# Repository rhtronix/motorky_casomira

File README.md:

motorky_casomira
================

Motorky - časomíra. BT displej, čtečky...

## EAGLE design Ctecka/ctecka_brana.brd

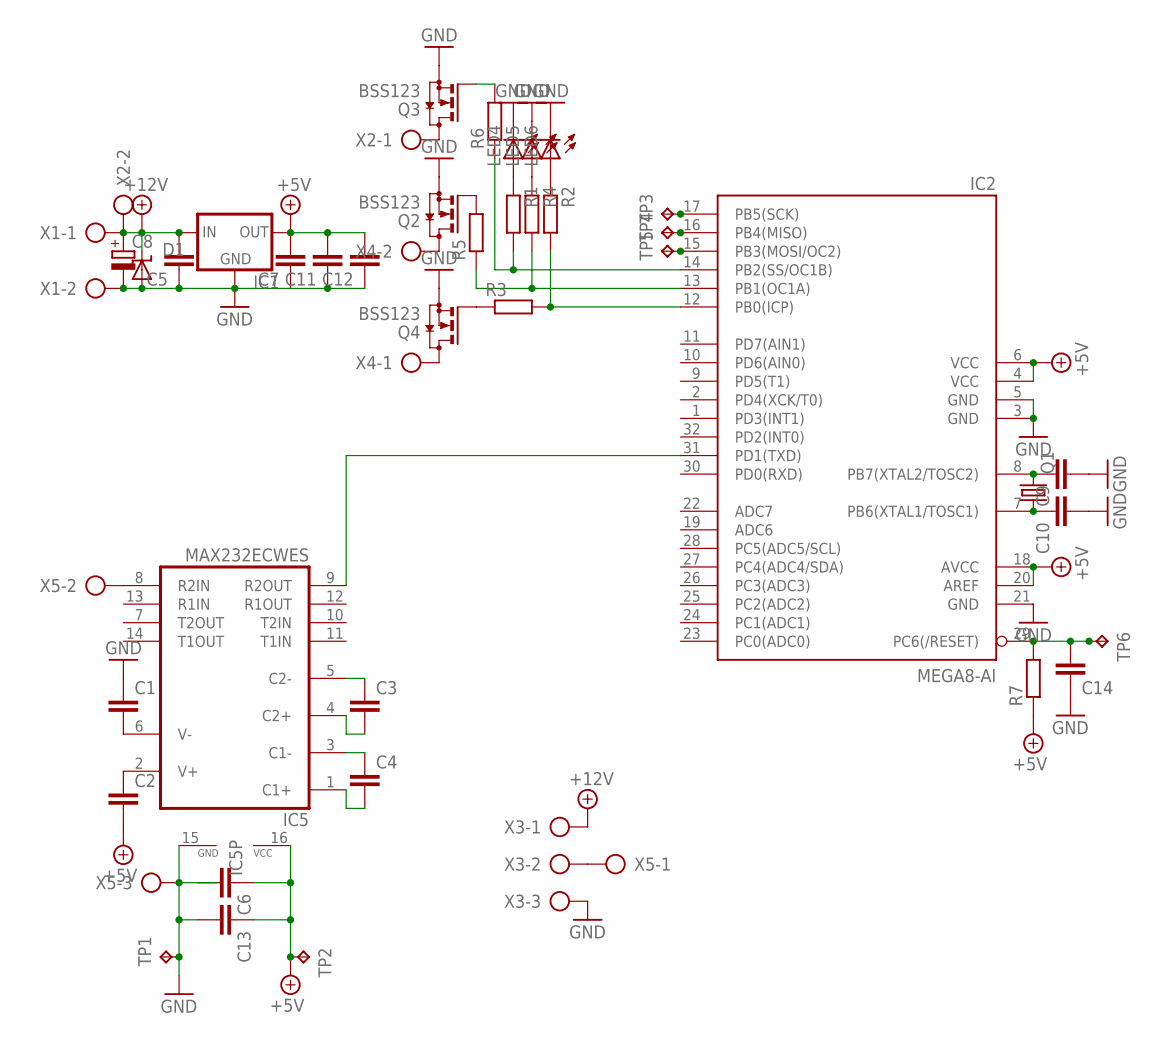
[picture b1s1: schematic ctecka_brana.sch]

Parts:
C1, C2, C3, C4, C5, C6, C7, C9, C10, C11, C12, C13, C14: C-EUC0603; C0603
C8: CPOL-EUSMCD; SMC_D
D1: SUPPRESSOR-SMBG; SMBG
IC1: 78LXXF; SOT89R
IC2: MEGA8-AI; TQFP32-08
IC5: MAX232ECWES; SO16
LED4, LED5, LED6: LEDCHIP-LED0805; CHIP-LED0805
Q1: CRYSTALCTS406; CTS406
Q2, Q3, Q4: BSS123; SOT23
R1, R2, R3, R4, R5, R6, R7: R-EU_R0603; R0603
TP1, TP2, TP3, TP4, TP5, TP6: TPB1,27; B1,27
X1, X2, X4: AK500/2
X3, X5: AK500/3

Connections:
+5V: C2.2, C6.1, C7.2, C11.2, C12.2, C13.1, IC1.2 (OUT), IC2.4 (VCC), IC2.6 (VCC), IC2.18 (AVCC), IC2.20 (AREF), IC5.16 (VCC), R7.1, TP2.TP
+12V: C5.2, C8.+, D1.C, IC1.1 (IN), X1.1, X2.2, X3.1
GND: C1.1, C5.1, C6.2, C7.1, C8.-, C9.2, C10.2, C11.1, C12.1, C13.2, C14.1, D1.A, IC1.3 (GND), IC2.3 (GND), IC2.5 (GND), IC2.21 (GND), IC5.15 (GND), LED4.C, LED5.C, LED6.C, Q2.2 (S), Q3.2 (S), Q4.2 (S), TP1.TP, X1.2, X3.3, X5.3
unnamed: IC2.17 (PB5(SCK)), TP3.TP
unnamed: IC2.15 (PB3(MOSI/OC2)), TP5.TP
unnamed: Q3.3 (D), X2.1
unnamed: IC2.31 (PD1(TXD)), IC5.9 (R2OUT)
unnamed: C3.1, IC5.5 (C2-)
unnamed: C4.1, IC5.3 (C1-)
unnamed: C1.2, IC5.6 (V-)
unnamed: C2.1, IC5.2 (V+)
unnamed: X3.2, X5.1
unnamed: IC5.8 (R2IN), X5.2
unnamed: C4.2, IC5.1 (C1+)
unnamed: C3.2, IC5.4 (C2+)
unnamed: IC2.16 (PB4(MISO)), TP4.TP
unnamed: C14.2, IC2.29 (PC6(/RESET)), R7.2, TP6.TP
unnamed: C9.1, IC2.8 (PB7(XTAL2/TOSC2)), Q1.3 (2)
unnamed: C10.1, IC2.7 (PB6(XTAL1/TOSC1)), Q1.1
unnamed: Q2.1 (G), R5.2
unnamed: Q2.3 (D), X4.2
unnamed: Q4.1 (G), R3.1
unnamed: Q4.3 (D), X4.1
unnamed: LED4.A, R1.1
unnamed: LED5.A, R4.1
unnamed: LED6.A, R2.1
unnamed: Q3.1 (G), R6.2
unnamed: IC2.12 (PB0(ICP)), R2.2, R3.2
unnamed: IC2.13 (PB1(OC1A)), R4.2, R5.1
unnamed: IC2.14 (PB2(SS/OC1B)), R1.2, R6.1

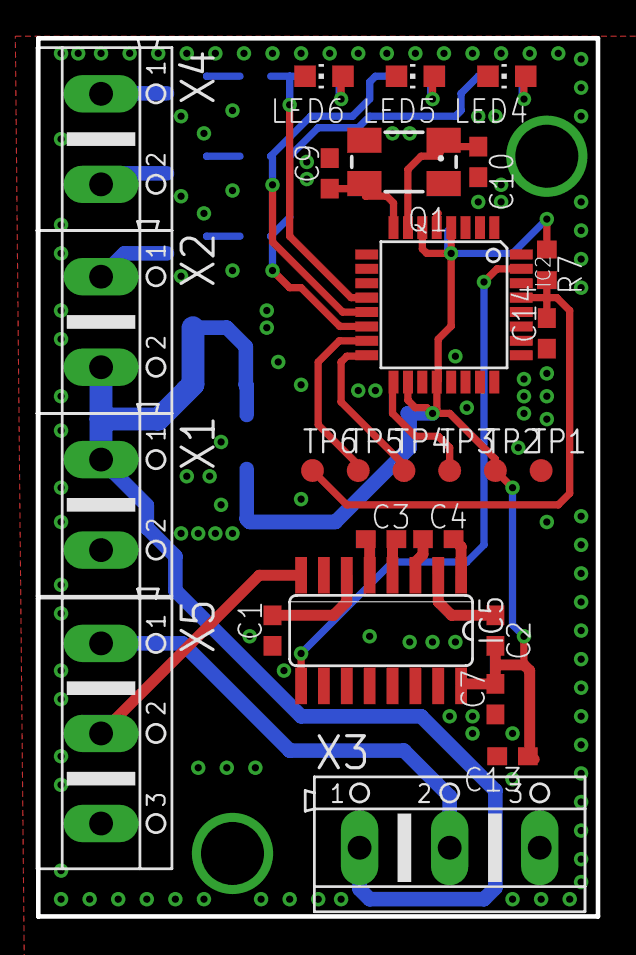
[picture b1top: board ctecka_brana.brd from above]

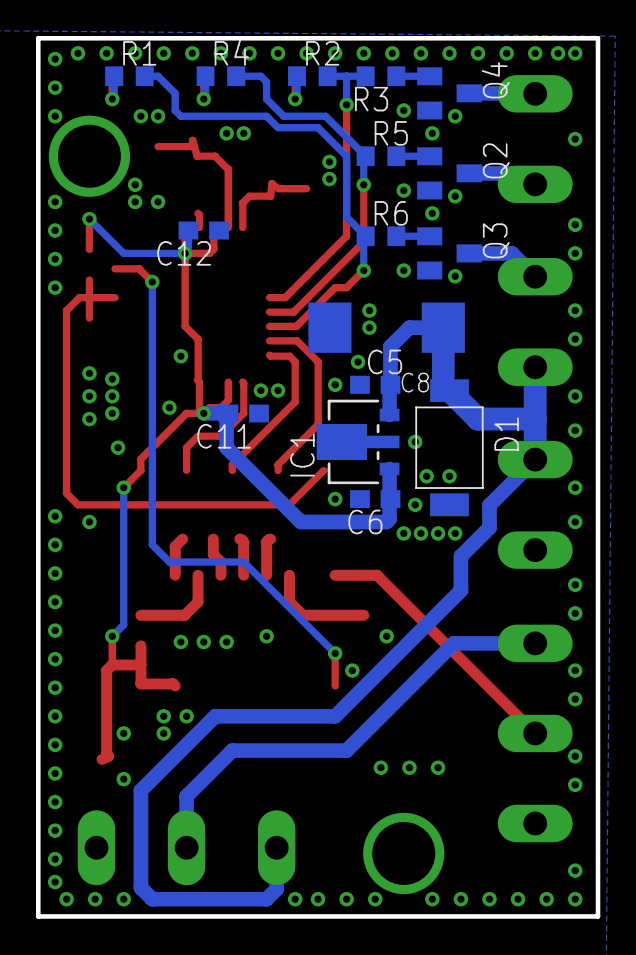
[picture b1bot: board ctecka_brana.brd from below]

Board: 2 copper layers, 31.1 x 48.8 mm, 43 parts (16 on the bottom side), 30 nets.

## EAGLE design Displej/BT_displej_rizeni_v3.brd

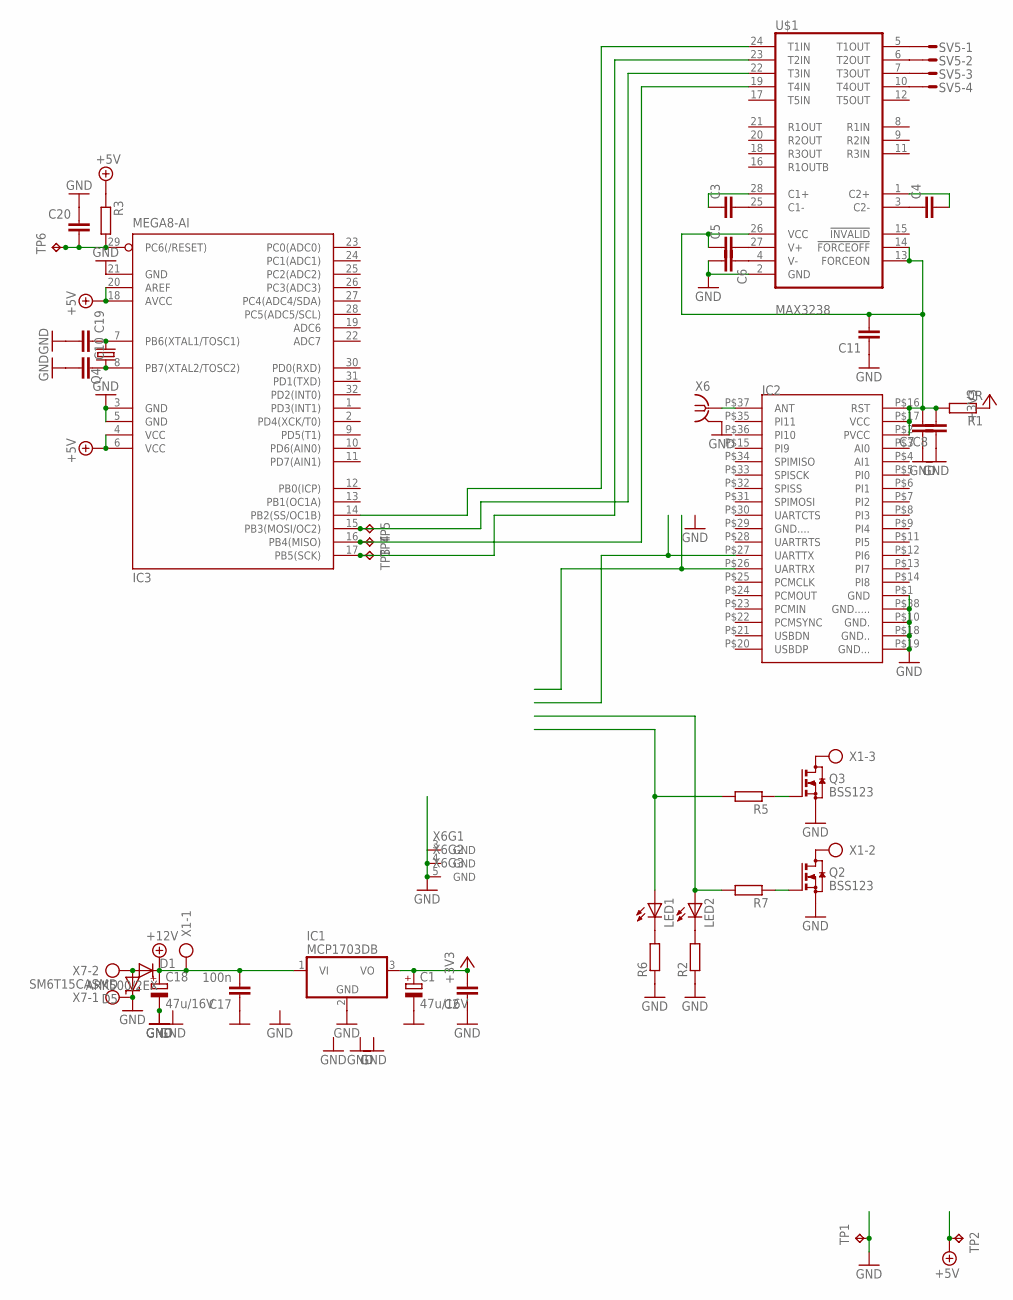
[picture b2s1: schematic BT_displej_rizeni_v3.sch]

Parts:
C1, C18: 47u/16V; SMC_C
C2, C3, C4, C5, C6, C7, C8, C10, C11, C19, C20: C-EUC0603; C0603
C17: 100n; C0603
D1: DIODE-DO214AC; DO214AC
D5: SM6T15CASMD; SMBJ
IC1: MCP1703DB; SOT223
IC2: BT220; B_DIL
IC3: MEGA8-AI; TQFP32-08
LED1, LED2: LEDCHIP-LED0805; CHIP-LED0805
Q2, Q3: BSS123; SOT23
Q4: CRYSTALCTS406; CTS406
R1: 0R; R0603
R2, R3, R5, R6, R7: R-EU_R0603; R0603
SV5: S04P
TP1, TP2, TP3, TP4, TP5, TP6: TPB1,27; B1,27
U$1: MAX3238; SSOP28
X1: AK500/3
X6: BU-SMA-V
X7: ARK500/2EX; AK500/2

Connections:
+3V3: C1.+, C2.2, IC1.3 (VO), R1.1
+5V: IC3.4 (VCC), IC3.6 (VCC), IC3.18 (AVCC), IC3.20 (AREF), R3.1, TP2.TP
+12V: C17.2, C18.+, D1.C, IC1.1 (VI), X1.1
GND: C1.-, C2.1, C6.2, C7.1, C8.1, C10.2, C11.1, C17.1, C18.-, C19.2, C20.1, D5.C, IC1.2 (GND), IC2.P$1 (GND), IC2.P$10 (GND.), IC2.P$18 (GND..), IC2.P$19 (GND...), IC2.P$38 (GND.....), IC3.3 (GND), IC3.5 (GND), IC3.21 (GND), Q2.2 (S), Q3.2 (S), R2.1, R6.1, TP1.TP, U$1.2 (GND), X6.2 (GND), X6.3 (GND), X6.4 (GND), X6.5 (GND), X7.1
unnamed: SV5.1, U$1.5 (T1OUT)
unnamed: LED2.C, R2.2
unnamed: Q3.1 (G), R5.1
unnamed: D1.A, D5.A, X7.2
unnamed: LED1.C, R6.2
unnamed: LED1.A, R5.2
unnamed: LED2.A, R7.2
unnamed: Q3.3 (D), X1.3
unnamed: Q2.3 (D), X1.2
unnamed: Q2.1 (G), R7.1
unnamed: SV5.2, U$1.6 (T2OUT)
unnamed: SV5.3, U$1.7 (T3OUT)
unnamed: SV5.4, U$1.10 (T4OUT)
unnamed: C3.2, U$1.25 (C1-)
unnamed: IC3.14 (PB2(SS/OC1B)), U$1.24 (T1IN)
unnamed: C4.1, U$1.3 (C2-)
unnamed: C3.1, U$1.28 (C1+)
unnamed: IC3.17 (PB5(SCK)), TP3.TP, U$1.23 (T2IN)
unnamed: IC3.15 (PB3(MOSI/OC2)), TP5.TP, U$1.22 (T3IN)
unnamed: IC3.16 (PB4(MISO)), TP4.TP, U$1.19 (T4IN)
unnamed: C4.2, U$1.1 (C2+)
unnamed: C5.2, U$1.27 (V+)
unnamed: C6.1, U$1.4 (V-)
unnamed: C5.1, C7.2, C8.2, C11.2, IC2.P$2 (PVCC), IC2.P$16 (RST), IC2.P$17 (VCC), R1.2, U$1.13 (FORCEON), U$1.14 (!FORCEOFF), U$1.26 (VCC)
unnamed: IC2.P$37 (ANT), X6.1
unnamed: C10.1, IC3.8 (PB7(XTAL2/TOSC2)), Q4.3 (2)
unnamed: C19.1, IC3.7 (PB6(XTAL1/TOSC1)), Q4.1
unnamed: C20.2, IC3.29 (PC6(/RESET)), R3.2, TP6.TP

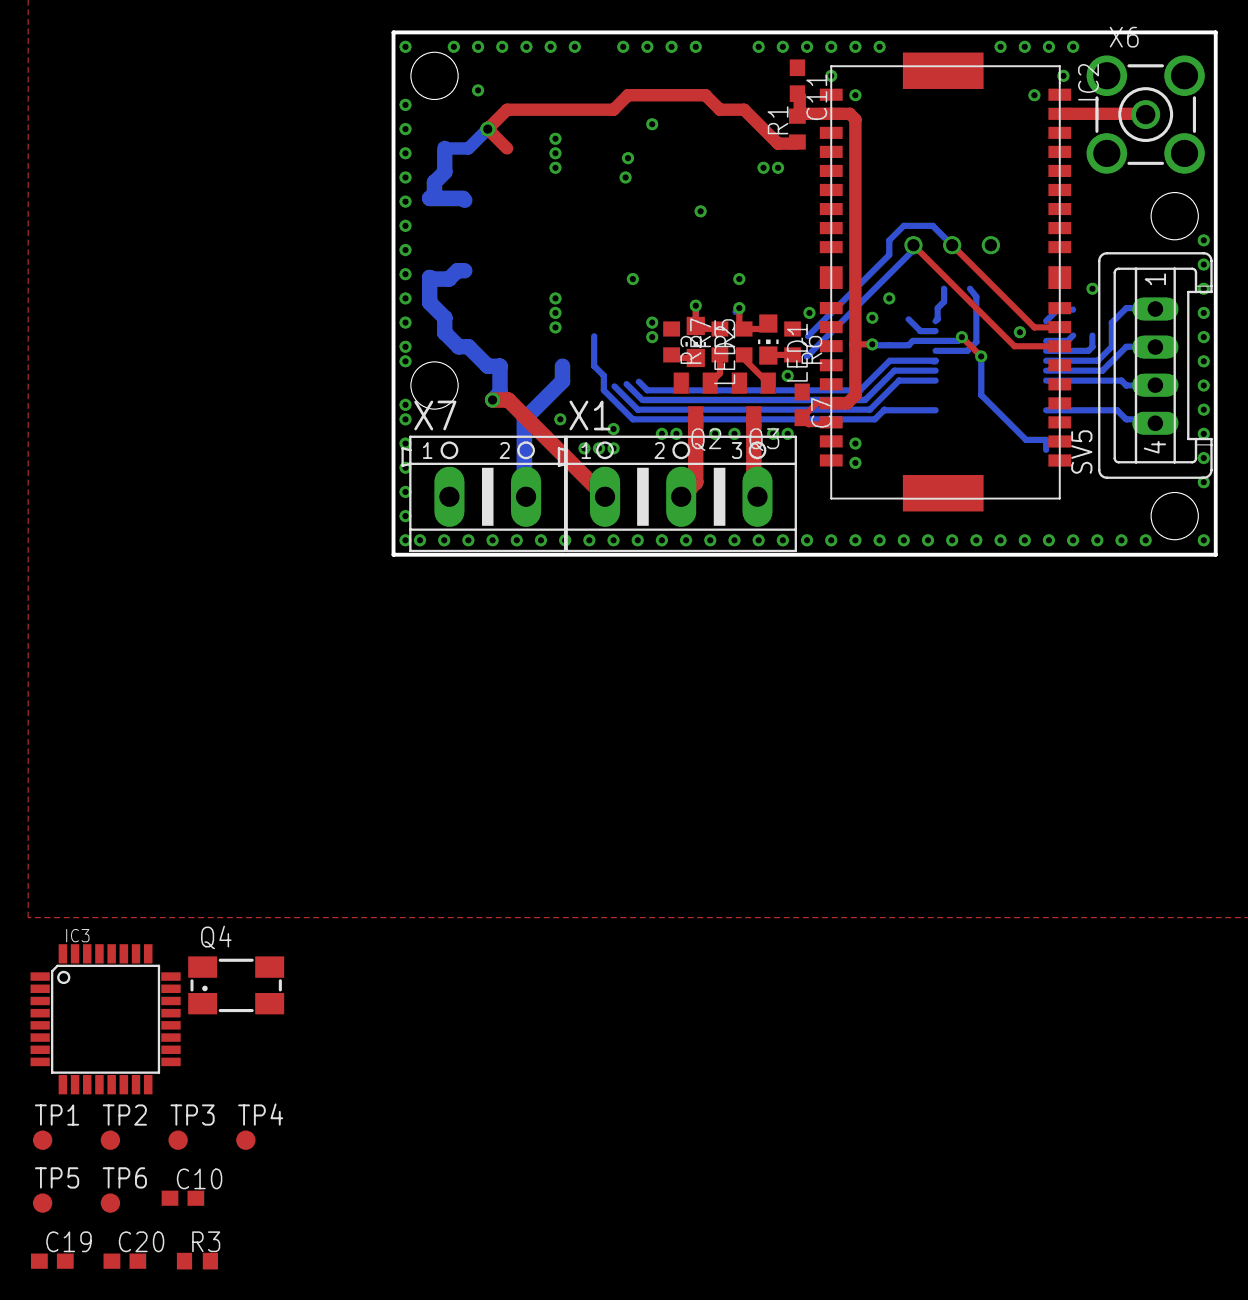
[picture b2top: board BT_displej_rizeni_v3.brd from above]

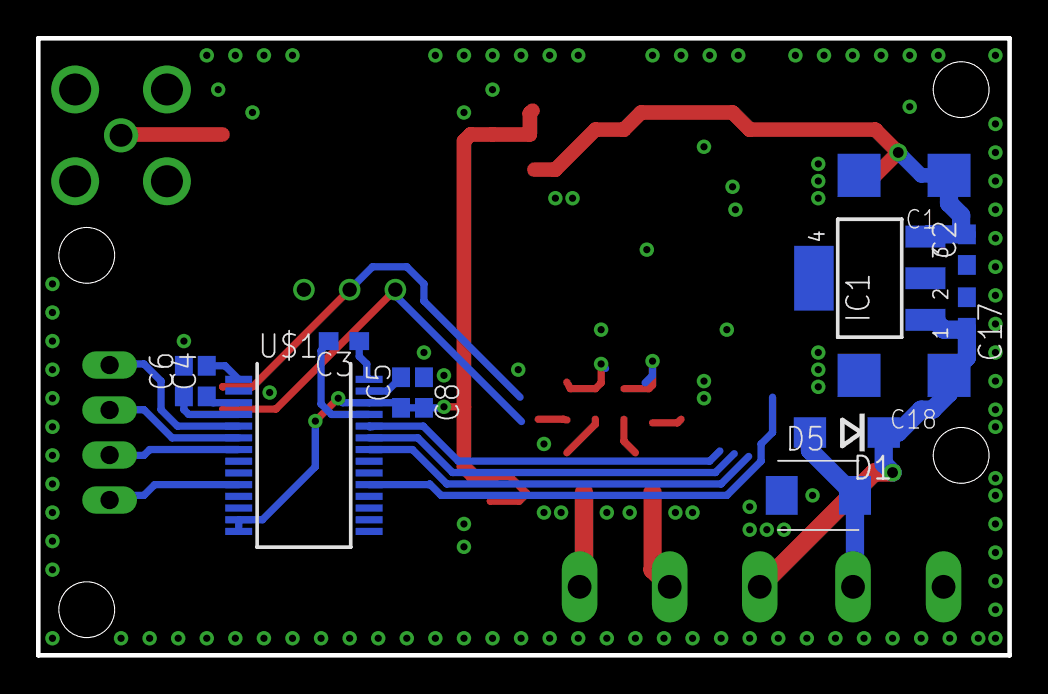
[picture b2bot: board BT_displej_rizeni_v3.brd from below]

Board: 2 copper layers, 54.0 x 34.3 mm, 41 parts (13 on the bottom side), 32 nets.

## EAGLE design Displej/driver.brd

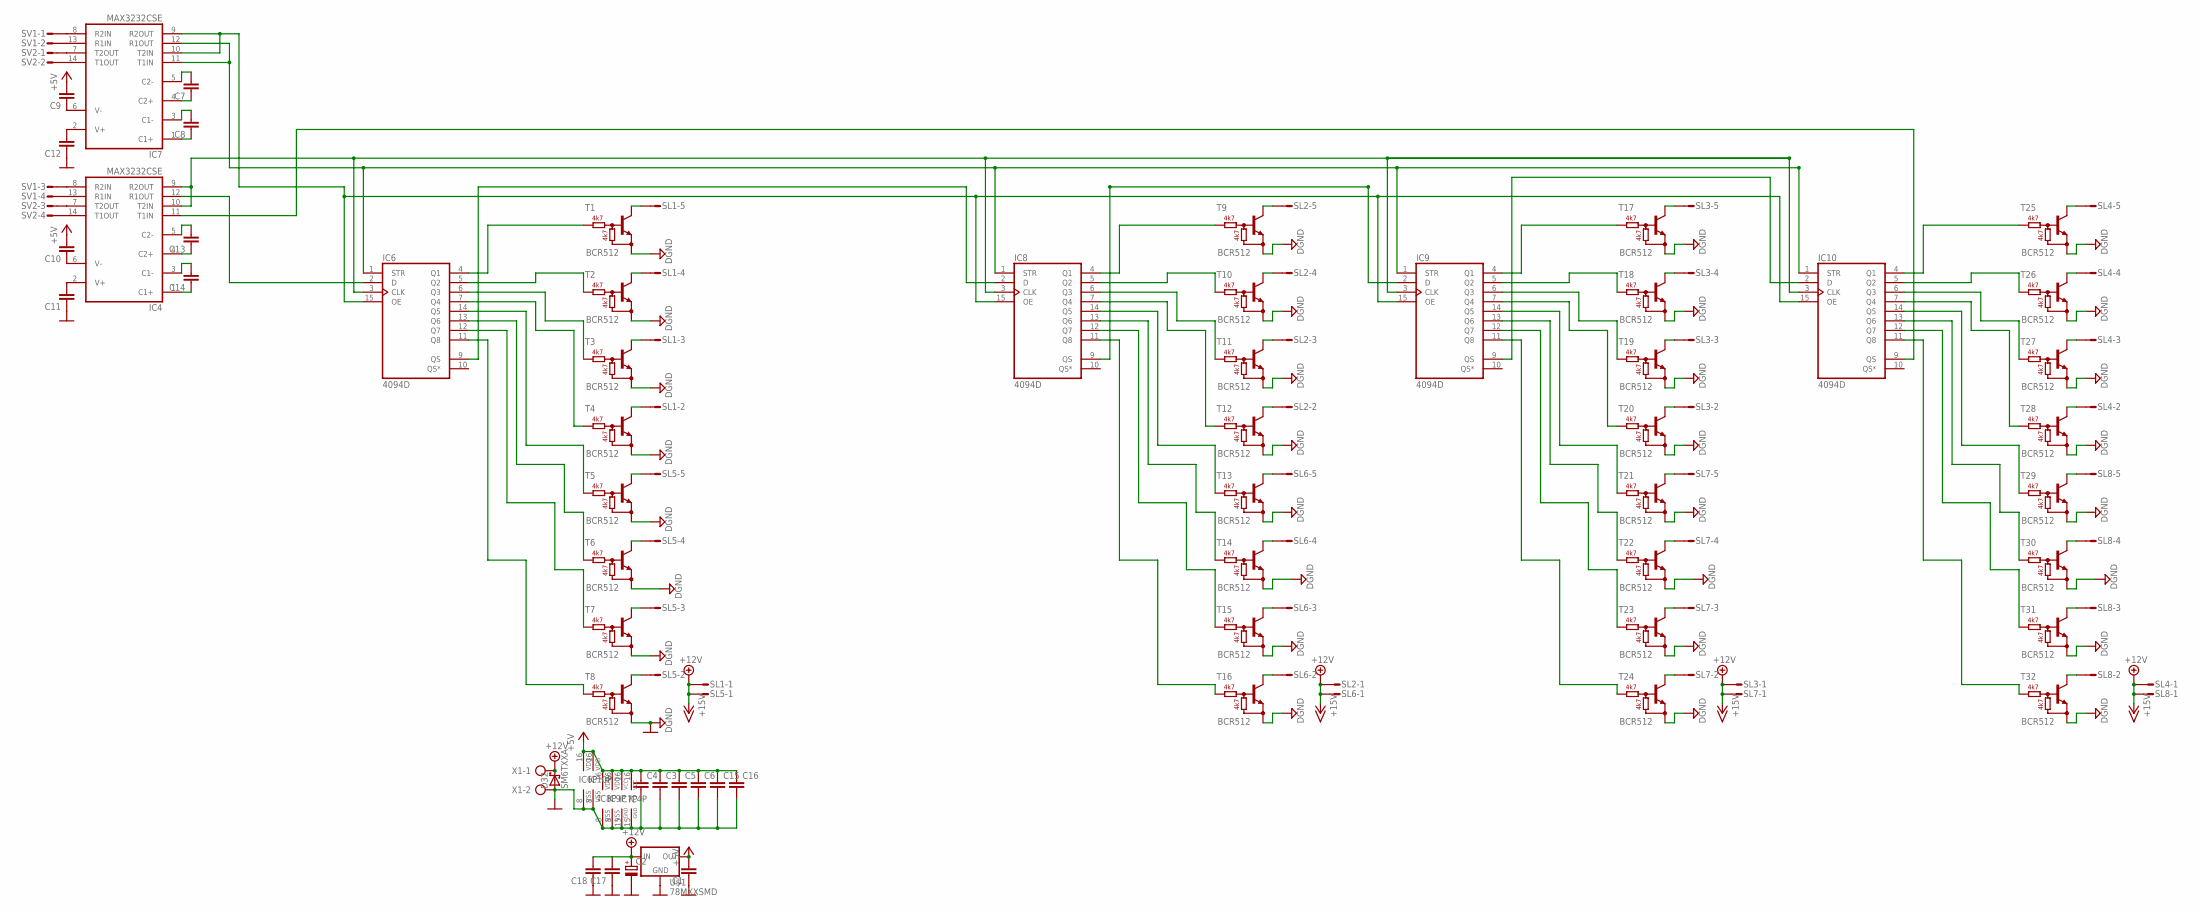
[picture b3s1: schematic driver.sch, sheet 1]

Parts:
C1, C3, C4, C5, C6, C7, C8, C9, C10, C11, C12, C13, C14, C15, C16, C17, C18: C-EUC0603; C0603
C2: CPOL-EUSMCD; SMC_D
D32: SM6TXXA; SMB
IC4, IC7: MAX3232CSE; SO16
IC6, IC8, IC9, IC10: 4094D; SO16
SL1, SL2, SL3, SL4, SL5, SL6, SL7, SL8: M05S; 05P
SV1, SV2: S04P
T1, T2, T3, T4, T5, T6, T7, T8, T9, T10, T11, T12, T13, T14, T15, T16, T17, T18, T19, T20, T21, T22, T23, T24, T25, T26, T27, T28, T29, T30, T31, T32: BCR512; SOT23-R_INFINEON
U$1: 78MXXSMD; DPACK
X1: AK500/2

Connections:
+5V: C1.2, C3.1, C4.1, C5.1, C6.1, C9.2, C10.2, C15.1, C16.1, IC4.16 (VCC), IC6.16 (VDD), IC7.16 (VCC), IC8.16 (VDD), IC9.16 (VDD), IC10.16 (VDD), U$1.3 (OUT)
+12V: C2.+, C17.2, C18.2, D32.C, SL1.1, SL2.1, SL3.1, SL4.1, SL5.1, SL6.1, SL7.1, SL8.1, U$1.1 (IN), X1.1
GND: C1.1, C2.-, C3.2, C4.2, C5.2, C6.2, C11.1, C12.1, C15.2, C16.2, C17.1, C18.1, D32.A, IC4.15 (GND), IC6.8 (VSS), IC7.15 (GND), IC8.8 (VSS), IC9.8 (VSS), IC10.8 (VSS), T1.2 (E), T2.2 (E), T3.2 (E), T4.2 (E), T5.2 (E), T6.2 (E), T7.2 (E), T8.2 (E), T9.2 (E), T10.2 (E), T11.2 (E), T12.2 (E), T13.2 (E), T14.2 (E), T15.2 (E), T16.2 (E), T17.2 (E), T18.2 (E), T19.2 (E), T20.2 (E), T21.2 (E), T22.2 (E), T23.2 (E), T24.2 (E), T25.2 (E), T26.2 (E), T27.2 (E), T28.2 (E), T29.2 (E), T30.2 (E), T31.2 (E), T32.2 (E), U$1.4 (GND), X1.2
unnamed: IC8.13 (Q6), T14.1 (B)
unnamed: IC8.4 (Q1), T9.1 (B)
unnamed: IC8.5 (Q2), T10.1 (B)
unnamed: IC8.11 (Q8), T16.1 (B)
unnamed: IC8.12 (Q7), T15.1 (B)
unnamed: IC8.14 (Q5), T13.1 (B)
unnamed: IC8.7 (Q4), T12.1 (B)
unnamed: IC8.6 (Q3), T11.1 (B)
unnamed: SL2.5, T9.3 (C)
unnamed: SL2.4, T10.3 (C)
unnamed: IC6.12 (Q7), T7.1 (B)
unnamed: SL6.5, T13.3 (C)
unnamed: SL6.4, T14.3 (C)
unnamed: SL6.3, T15.3 (C)
unnamed: SL6.2, T16.3 (C)
unnamed: SL2.2, T12.3 (C)
unnamed: SL2.3, T11.3 (C)
unnamed: IC9.9 (QS), IC10.2 (D)
unnamed: IC10.13 (Q6), T30.1 (B)
unnamed: IC10.4 (Q1), T25.1 (B)
unnamed: IC8.9 (QS), IC9.2 (D)
unnamed: IC4.11 (T1IN), IC10.9 (QS)
unnamed: IC9.13 (Q6), T22.1 (B)
unnamed: IC7.8 (R2IN), SV1.1
unnamed: IC9.4 (Q1), T17.1 (B)
unnamed: C7.1, IC7.4 (C2+)
unnamed: IC9.5 (Q2), T18.1 (B)
unnamed: IC9.11 (Q8), T24.1 (B)
unnamed: IC9.12 (Q7), T23.1 (B)
unnamed: IC9.14 (Q5), T21.1 (B)
unnamed: IC9.7 (Q4), T20.1 (B)
unnamed: IC9.6 (Q3), T19.1 (B)
unnamed: SL3.5, T17.3 (C)
unnamed: SL3.4, T18.3 (C)
unnamed: SL7.5, T21.3 (C)
unnamed: SL7.4, T22.3 (C)
unnamed: SL7.3, T23.3 (C)
unnamed: SL7.2, T24.3 (C)
unnamed: SL3.2, T20.3 (C)
unnamed: SL3.3, T19.3 (C)
unnamed: IC6.1 (STR), IC7.11 (T1IN), IC7.12 (R1OUT), IC8.1 (STR), IC9.1 (STR), IC10.1 (STR)
unnamed: IC4.12 (R1OUT), IC6.2 (D)
unnamed: IC10.5 (Q2), T26.1 (B)
unnamed: IC10.11 (Q8), T32.1 (B)
unnamed: IC10.12 (Q7), T31.1 (B)
unnamed: IC10.14 (Q5), T29.1 (B)
unnamed: IC10.7 (Q4), T28.1 (B)
unnamed: IC7.13 (R1IN), SV1.2
unnamed: IC10.6 (Q3), T27.1 (B)
unnamed: SL4.5, T25.3 (C)
unnamed: SL4.4, T26.3 (C)
unnamed: SL8.5, T29.3 (C)
unnamed: IC4.8 (R2IN), SV1.3
unnamed: SL8.4, T30.3 (C)
unnamed: SL8.3, T31.3 (C)
unnamed: SL8.2, T32.3 (C)
unnamed: SL4.2, T28.3 (C)
unnamed: SL4.3, T27.3 (C)
unnamed: IC6.15 (OE), IC7.9 (R2OUT), IC7.10 (T2IN), IC8.15 (OE), IC9.15 (OE), IC10.15 (OE)
unnamed: IC6.14 (Q5), T5.1 (B)
unnamed: IC4.9 (R2OUT), IC4.10 (T2IN), IC6.3 (CLK), IC8.3 (CLK), IC9.3 (CLK), IC10.3 (CLK)
unnamed: IC4.13 (R1IN), SV1.4
unnamed: IC6.7 (Q4), T4.1 (B)
unnamed: IC7.7 (T2OUT), SV2.1
unnamed: C8.1, IC7.1 (C1+)
unnamed: IC6.6 (Q3), T3.1 (B)
unnamed: SL1.5, T1.3 (C)
unnamed: SL1.4, T2.3 (C)
unnamed: SL5.5, T5.3 (C)
unnamed: SL5.4, T6.3 (C)
unnamed: SL5.3, T7.3 (C)
unnamed: SL5.2, T8.3 (C)
unnamed: IC6.13 (Q6), T6.1 (B)
unnamed: IC6.4 (Q1), T1.1 (B)
unnamed: IC6.5 (Q2), T2.1 (B)
unnamed: SL1.2, T4.3 (C)
unnamed: SL1.3, T3.3 (C)
unnamed: IC7.14 (T1OUT), SV2.2
unnamed: IC4.7 (T2OUT), SV2.3
unnamed: IC6.9 (QS), IC8.2 (D)
unnamed: IC4.14 (T1OUT), SV2.4
unnamed: IC6.11 (Q8), T8.1 (B)
unnamed: C13.1, IC4.4 (C2+)
unnamed: C14.1, IC4.1 (C1+)
unnamed: C12.2, IC7.2 (V+)
unnamed: C9.1, IC7.6 (V-)
unnamed: C11.2, IC4.2 (V+)
unnamed: C10.1, IC4.6 (V-)
unnamed: C7.2, IC7.5 (C2-)
unnamed: C8.2, IC7.3 (C1-)
unnamed: C13.2, IC4.5 (C2-)
unnamed: C14.2, IC4.3 (C1-)

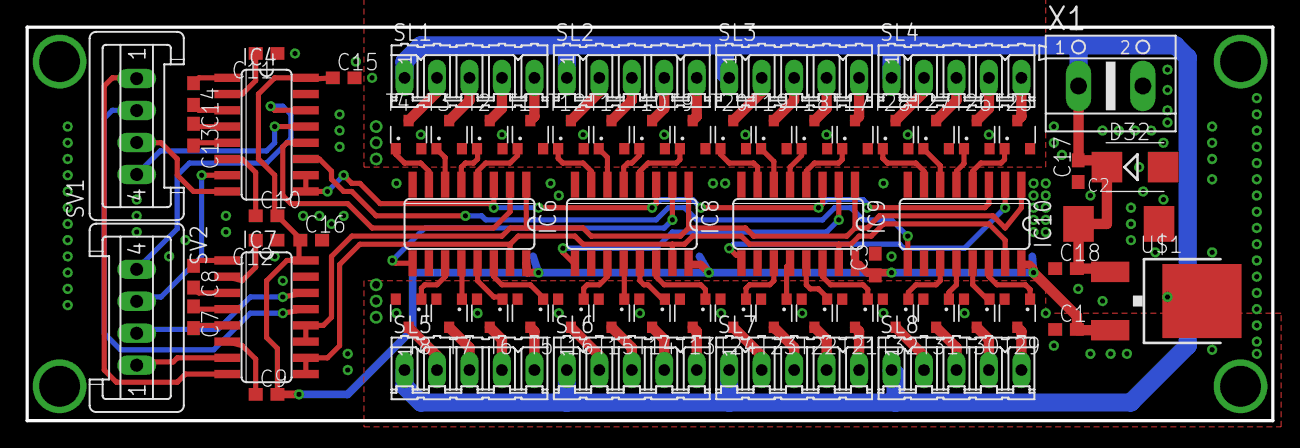
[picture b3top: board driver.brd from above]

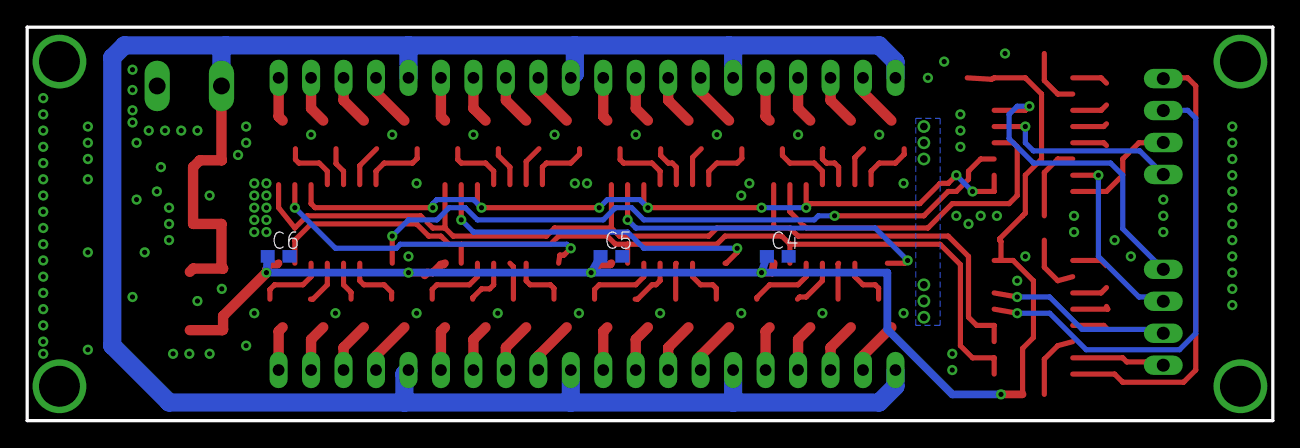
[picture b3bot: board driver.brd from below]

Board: 2 copper layers, 97.5 x 30.8 mm, 69 parts (3 on the bottom side), 95 nets.

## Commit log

2014-04-11 HW soubory pro rizeni a driver displeje
2014-04-13 new file: Ctecka/ctecka_brana.brd new file: Ctecka/ctecka_brana.sch new file: Ctecka/ctecka_mala.brd new file: Ctecka/ctecka_mala.sch new file: Ctecka/ctecka_stolni.brd new file: Ctecka/ctecka_stolni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
